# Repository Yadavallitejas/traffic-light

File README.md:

###Documentation of the Traffic Light system

This documentation provides a detailed explanation of each section of the traffic light project, utilizing components like the **ATmega328P microcontroller**, **7-segment displays**, **CD4511BE driver IC**, **power supply circuitry**, **RGB LED**, and other components. Below, we’ll break down each part of the circuit, their purpose, and how they work together to achieve the goal of controlling a traffic light system.

---

### **1. Power Supply Section**

#### Components:
- **7805 Voltage Regulator (U3)**
- **Diodes (D1)**
- **Capacitors (C1, C2, C3, C4, C5)**

#### Explanation:
- **7805 Voltage Regulator** is used to step down the input voltage (typically from a 9V or 12V source) to a stable 5V for powering the circuit.
- **D1 (1N4007)**: Protects the circuit from reverse polarity in case of incorrect power connections.
- **Capacitors (C1: 100μF, C2: 100μF, C3: 0.1μF, C4: 0.1μF)**: These are filtering capacitors used to smooth out any voltage ripples at the input and output of the regulator, ensuring stable 5V output.
- **LED**: A power indicator LED is connected with a current-limiting resistor to visually indicate when the circuit is powered.

---

### **2. ATmega328P Microcontroller (U1)**

#### Purpose:
The **ATmega328P** is the central controller of the traffic light system. It receives input signals, processes them, and controls the outputs such as the 7-segment display, RGB LED, and any other external components.

#### Key Connections:
- **Power Supply**: VCC and GND pins are connected to the 5V and ground lines, respectively.
- **Crystal Oscillator (XT1)**: A 16 MHz crystal oscillator is connected to pins XTAL1 and XTAL2 with two 22pF capacitors for timing purposes.
- **RESET Pin**: A pull-up resistor (R8, 10kΩ) ensures that the ATmega328P does not reset unintentionally.
  
#### Input/Output Pins:
- **RGB LED Control**: The ATmega328P controls the RGB LED by sending signals to the corresponding R, G, B lines (pins PB0, PB1, PB2).
- **7-Segment Control**: The microcontroller sends BCD (Binary-Coded Decimal) values to the CD4511BE driver to control the 7-segment displays.

#### Programming & Debugging:
- **ISP Header**: A 6-pin header is provided for In-System Programming (ISP) of the ATmega328P. This allows for easy programming and debugging without removing the microcontroller from the circuit. It connects to the MISO, MOSI, SCK, and RESET pins.

---

### **3. CD4511BE - BCD to 7-Segment Driver (U2)**

#### Purpose:
The **CD4511BE** is a BCD (Binary Coded Decimal) to 7-segment display decoder/driver. It takes BCD input from the microcontroller and converts it into the appropriate signals to drive the segments of a common cathode 7-segment display.

#### Key Connections:
- **BCD Input Pins (A, B, C, D)**: These are connected to the output pins of the ATmega328P to receive the BCD signals.
- **Segment Output Pins (a, b, c, d, e, f, g)**: These pins are connected to the corresponding segments of the 7-segment display.
- **Common Cathode Pin**: Connected to ground, this pin allows the control of all the segments through the CD4511BE.
- **LE (Latch Enable)**: Used to control when the output is updated.
- **Outputs**: Controls the SSD (7-segment display) to display numbers (0–9) as part of the traffic light timer.

---

### **4. 7-Segment Displays (SSD1 and SSD2)**

#### Purpose:
The **7-segment displays** are used to display the countdown or time remaining for each traffic light state. This helps visualize the time before the light changes from green to red or vice versa.

#### Key Connections:
- **Cathodes**: The common cathode of the display is connected to ground.
- **Segments**: Each segment (a, b, c, d, e, f, g) is connected to the outputs of the CD4511BE decoder, which controls the display based on the BCD inputs from the ATmega328P.

---

### **5. RGB LED (Q3)**

#### Purpose:
The **RGB LED** is used to represent the traffic lights with red, green, and blue color options. By controlling the intensity of the different colors, the system can simulate the standard traffic light colors: Red (Stop), Green (Go), and Yellow (Caution).

#### Key Connections:
- **R, G, B Lines**: Each color channel (Red, Green, and Blue) is connected to the ATmega328P via current-limiting resistors (R31, R32, R33).
- **Control**: The microcontroller can control the brightness of each color using PWM (Pulse Width Modulation) to adjust the duty cycle, creating different shades and intensities.

---

### **6. Motor Drivers (L293D - not explicitly shown)**

If motor control is required for automated movements (e.g., for controlling barriers), the **L293D H-bridge motor driver** can be integrated into the design. It would control the direction and speed of DC motors by receiving signals from the ATmega328P. The motor driver would likely be powered from the same 5V rail or a separate higher voltage line for motors.

---

### **7. Power LED**

A simple power indicator LED connected in series with a current-limiting resistor, connected to the 5V line, provides a visual indication that the circuit is powered on.

---

### **8. Mounting Holes**

Several mounting holes (marked **MOUNTHOLE2.8**) are included to mechanically secure the PCB to an enclosure or surface, ensuring the board stays fixed during operation.

---

### **Software and Programming**

To operate the traffic light system, a program will need to be loaded onto the ATmega328P microcontroller. Here is a basic outline of the software logic:

#### **Traffic Light Control Algorithm**:
1. **Initialization**: Setup pin modes for the RGB LED, 7-segment display outputs, and the potentiometer input.
2. **Main Loop**:
   - Read the potentiometer value to determine the duration of each traffic light state.
   - Set the RGB LED to **Red** and start the timer countdown, displaying the time on the 7-segment displays.
   - After the timer expires, switch the RGB LED to **Green** and update the 7-segment displays accordingly.
   - Optionally, use **Yellow** as a transition between Red and Green.

### **Conclusion**

This traffic light system is based on a microcontroller (ATmega328P) and uses visual indicators (RGB LED and 7-segment displays) to simulate traffic signals. The circuit integrates standard components like the **CD4511BE** decoder for BCD-to-7-segment control, a regulated **5V power supply** and a robust power circuit, this project is a scalable and educational model of a real-world traffic light system.

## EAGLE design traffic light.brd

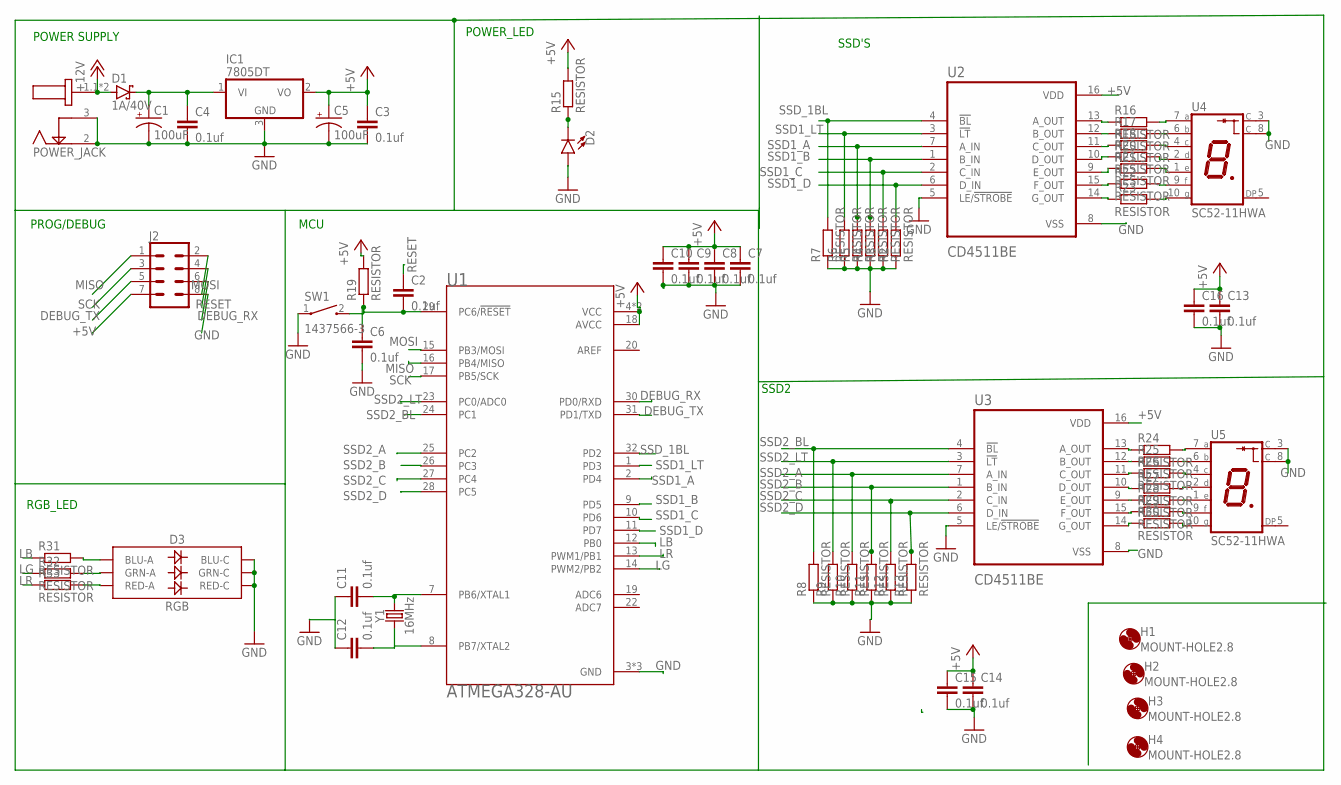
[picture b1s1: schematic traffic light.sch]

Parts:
C1, C5: 100uF; PANASONIC_D
C2, C4, C6, C11, C12: 0.1uf; C2.5-2
C3, C7, C8, C9, C10, C13, C14, C15, C16: 0.1uf; C2.5-3
D1: 1A/40V; C4111-15
D2: LED0603; LED-0603
D3: RGB; PLCC-6-LED
H1, H2, H3, H4: MOUNT-HOLE2.8; 2,8
IC1: 7805DT; TO252
J2: CONN_04X2; 2X4
POWER_JACK: DCJ200-05-A-XX-X_REVA; GCT_DCJ200-05-A-XX-X_REVA
R2, R3, R4, R5, R6, R7, R8, R9, R10, R11, R12, R13, R15, R16, R17, R18, R19, R20, R21, R22, R23, R24, R25, R26, R27, R28, R29, R30, R31, R32, R33: RESISTOR; R0603
SW1: 1437566-3; SW_1437566-3
U1: ATMEGA328-AU; QFP80P900X900X120-32N
U2, U3: CD4511BE; DIP794W45P254L1969H508Q16
U4, U5: SC52-11HWA; LED_SC52-11HWA
Y1: 16MHz; HC49US

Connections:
+5V: C3.1, C5.+, C7.1, C8.1, C9.1, C10.1, C13.1, C14.1, C15.1, C16.1, IC1.2 (VO), J2.7, R15.2, R19.2, U1.4 (VCC), U1.6 (VCC), U1.18 (AVCC), U2.16 (VDD), U3.16 (VDD)
+12V: D1.A, POWER_JACK.1.1 (1), POWER_JACK.1.2 (1)
DEBUG_RX: J2.6, U1.30 (PD0/RXD)
DEBUG_TX: J2.5, U1.31 (PD1/TXD)
GND: C1.-, C3.2, C4.2, C5.-, C6.2, C7.2, C8.2, C9.2, C10.2, C13.2, C14.2, C15.2, C16.2, D2.A, D3.CB (BLU-C), D3.CG (GRN-C), D3.CR (RED-C), IC1.3 (GND), J2.8, POWER_JACK.2, POWER_JACK.3, R2.1, R3.1, R4.1, R5.1, R6.1, R7.1, R8.1, R9.1, R10.1, R11.1, R12.1, R13.1, SW1.1, U1.3 (GND), U1.5 (GND), U1.21 (GND), U2.5 (LE/!STROBE), U2.8 (VSS), U3.5 (LE/!STROBE), U3.8 (VSS), U4.3 (C), U4.8 (C), U5.3 (C), U5.8 (C)
LB: R31.1, U1.12 (PB0)
LG: R32.1, U1.14 (PWM2/PB2)
LR: R33.1, U1.13 (PWM1/PB1)
MISO: J2.1, U1.16 (PB4/MISO)
MOSI: J2.2, U1.15 (PB3/MOSI)
unnamed: C1.+, C4.1, D1.C, IC1.1 (VI)
unnamed: D3.AB (BLU-A), R31.2
unnamed: D3.AG (GRN-A), R32.2
unnamed: D2.C, R15.1
unnamed: R16.1, U2.13 (A_OUT)
unnamed: R16.2, U4.7 (A)
unnamed: R17.2, U4.6 (B)
unnamed: R17.1, U2.12 (B_OUT)
unnamed: R18.1, U2.11 (C_OUT)
unnamed: R20.1, U2.10 (D_OUT)
unnamed: R21.1, U2.9 (E_OUT)
unnamed: R22.1, U2.15 (F_OUT)
unnamed: R24.1, U3.13 (A_OUT)
unnamed: R24.2, U5.7 (A)
unnamed: R25.1, U3.12 (B_OUT)
unnamed: R26.1, U3.11 (C_OUT)
unnamed: R27.1, U3.10 (D_OUT)
unnamed: R28.1, U3.9 (E_OUT)
unnamed: R29.1, U3.15 (F_OUT)
unnamed: C2.2, C6.1, R19.1, SW1.2, U1.29 (PC6/!RESET)
unnamed: C11.2, U1.7 (PB6/XTAL1), Y1.2
unnamed: C12.2, U1.8 (PB7/XTAL2), Y1.1
unnamed: C11.1, C12.1
unnamed: R23.1, U2.14 (G_OUT)
unnamed: R18.2, U4.4 (C)
unnamed: R20.2, U4.2 (D)
unnamed: R21.2, U4.1 (E)
unnamed: R22.2, U4.9 (F)
unnamed: R23.2, U4.10 (G)
unnamed: R30.1, U3.14 (G_OUT)
unnamed: R30.2, U5.10 (G)
unnamed: R29.2, U5.9 (F)
unnamed: R25.2, U5.6 (B)
unnamed: R26.2, U5.4 (C)
unnamed: R27.2, U5.2 (D)
unnamed: R28.2, U5.1 (E)
unnamed: D3.AR (RED-A), R33.2
RESET: C2.1, J2.4
SCK: J2.3, U1.17 (PB5/SCK)
SSD1_A: R5.2, U1.2 (PD4), U2.7 (A_IN)
SSD1_B: R4.2, U1.9 (PD5), U2.1 (B_IN)
SSD1_C: R3.2, U1.10 (PD6), U2.2 (C_IN)
SSD1_D: R2.2, U1.11 (PD7), U2.6 (D_IN)
SSD1_LT: R6.2, U1.1 (PD3), U2.3 (!LT)
SSD2_A: R10.2, U1.25 (PC2), U3.7 (A_IN)
SSD2_B: R11.2, U1.26 (PC3), U3.1 (B_IN)
SSD2_BL: R8.2, U1.24 (PC1), U3.4 (!BL)
SSD2_C: R12.2, U1.27 (PC4), U3.2 (C_IN)
SSD2_D: R13.2, U1.28 (PC5), U3.6 (D_IN)
SSD2_LT: R9.2, U1.23 (PC0/ADC0), U3.3 (!LT)
SSD_1BL: R7.2, U1.32 (PD2), U2.4 (!BL)

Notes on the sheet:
POWER SUPPLY
RGB_LED
SSD'S
PROG/DEBUG
POWER_LED
SSD2
MCU

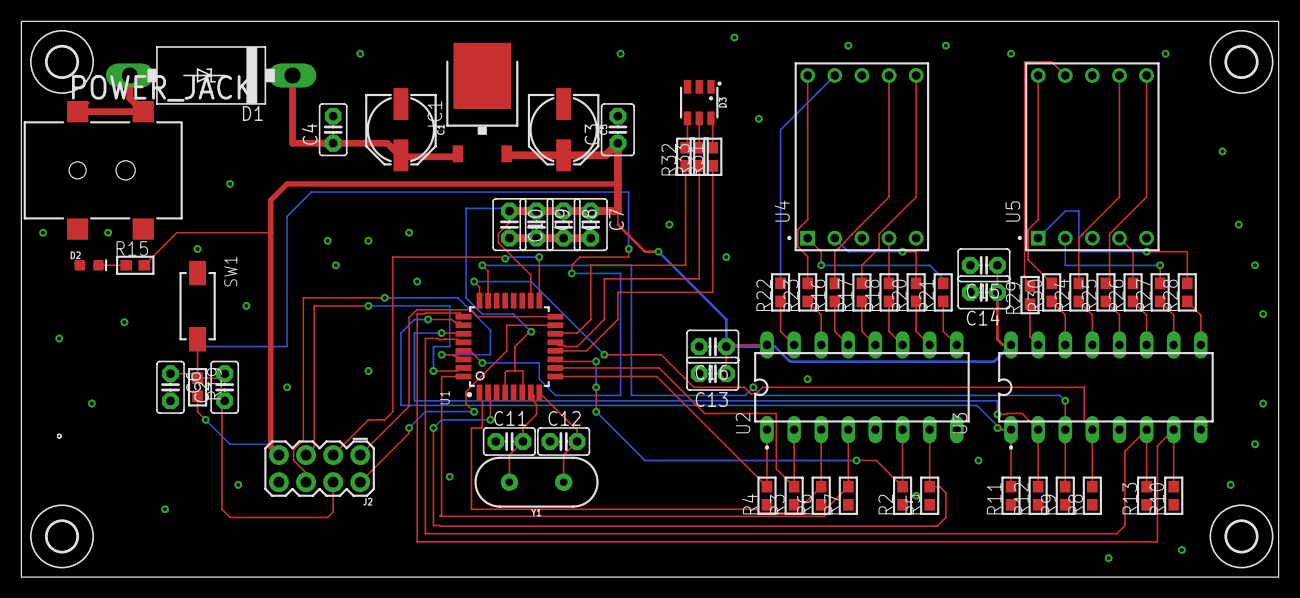
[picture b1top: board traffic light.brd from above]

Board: 2 copper layers, 117.8 x 52.1 mm, 64 parts (0 on the bottom side), 61 nets.

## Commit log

2024-10-11 Documentation README.md

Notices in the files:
parts and their libraries:
SparkFun-Capacitors: Licensing: Creative Commons ShareAlike 4.0 International - https://creativecommons.org/licenses/by-sa/4.0
